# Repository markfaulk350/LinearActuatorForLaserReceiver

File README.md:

# Linear Actuator For Laser Receiver

# Todo
- See if we can use the DF Robot Voice Recognition to controll the whole thing. Look at the [pre-programmed keywords](https://wiki.dfrobot.com/SKU_SEN0539-EN_Gravity_Voice_Recognition_Module_I2C_UART#Command%20Words%2FWake-up%20Words%20%26amp%3B%20ID%20Table) to see what would work best.
- Get 4x M3 bolts for the motor. The depth is 4.5mm (0.17 in), so add the thickness of the plate. M3 x 0.5 x 8mm is best for a 0.2in plate.
- Get 3x M3 x 0.5 x 16mm bolts for the lead screw flange nut. Model the carriage so they can thread into the plastic. The flange is 0.19in thick so .6 in or 16mm is probably good. 12mm long might work but just barely, try 16mm at lowes.
- Order limit switches
- Order a linear rail. Or see if we can use the 2040 instead with a 3d printed solution.
- Order 2mm right angle pcb connector and male connector w wires
- Maybe make your own M18 adapter and put all the electronics inside it, boost converter, fuse, arduino, buck converter for arduino, etc.
- Order or make a 5mm to 3/8 coupler
- 3d print a qd mount for the laser receiver

## Custom Sensor Array vs Standard Laser Receiver on Linear Actuator
A Custom CCD or photodiode array is going to be too expensive, time consuming, and it might not work with every laser. 

On the Job, we are already moving the stick up and down, and tilting it to get the laser receiver to beep.

I propose we just hold the stick still, and have a linear actuator move the standard laser receiver until it beeps. We can tie into the laser receivers speaker wires and use that to position it perfectly. Once it's positioned, we can give the user the measurement.

### Linear Actuator
### Pros
- Cheap
- Simple to program
- Technology already exists
- Can be expanded to any length cheaply
- Can mount any laser receiver

### Cons
- Bulky
- Heavier
- Requires more power
- The physical size of the laser receiver affects the total scan area. And user needs to set the max extension so that it doesn't crash the laser receiver into the enclosure.
- Scanning is slower. 1ft per second is acceptable
  - Scanning speed largely depends on how quickly the laser receiver can detect the laser. 
- The UI is more complicated. (Calibrate, Jog, "Home", Scan)
- Different laser receivers have different speakers and signals
- If the laser receiver moves up and down, we either need to listen for the (fast, solid, slow) beeps using a microphone, or tap into the speaker wires.
- If we tap into the speaker wires, we will need to make a little radio to transmit the speaker signals to our esp32. The laser receiver will be moving up and down, we cant use a wire, it would snag or break.

# Build requirements
- Needs to scan quickly. 1ft per second is a good speed.
- Needs to move a 300g laser reeciver up and down.
- No creep. If bumped, powered off, etc. Belt drive probably wont work.
- 2 to 3 ft scan area
- Total weight under 5 pounds. Loose requirement.
- Needs to work in a dusty, hot environment.
- Encoder on stepper motor for exact position
- Maybe boost convertor for higher speeds

# Laser Receiver Dimensions
- Topcon LS-80L (NEW Model)
  - x in (Tall) | x in (Wide) | x in (Thick) | x grams (Weight)
- Topcon LS-70B (OLD Model)
  - 6.5 in (Tall) | 3 in (Wide) | 1.05 in (Thick) | 220 grams (Weight)

# Parts List
- $71 | [StepperOnline | ESS17-04](https://www.omc-stepperonline.com/ess-series-0-48nm-68oz-in-nema-17-integrated-closed-loop-stepper-servo-motor-24-36vdc-1000cpr-ess17-04)
  - [3D Model .IGS](https://www.omc-stepperonline.com/index.php?route=product/product/get_file&file=1265/ESS17-04.IGS)
  - Input Voltage: 24 - 36VDC
  - Weight: 419g
  - [SpecSheet](file:///Users/markfaulkner/Downloads/ESS17-04_07_Manual.pdf)
- $83 | [M18 HIGH OUTPUT CP3.0](https://www.milwaukeetool.com/products/48-11-1835)
  - Weight: 595g
- $8 | [M18 Adapter | Amazon](https://a.co/d/7E8KwFV)
  - Weight: 80g
- $57 | [300W Boost Converter | I7C4W008A120V-001-R | Digikey](https://www.digikey.com/en/products/detail/tdk-lambda/I7C4W008A120V-001-R/11697408)
  - Weight: 25g, 1.5 x 1.5 x 0.5 inches
  - Output Voltage: 9.6 to 48V
  - [SpecSheet](https://product.tdk.com/en/search/power/switching-power/dc-dc-converter/info?part_no=i7C4W008A120V-001-R)
- $40 | [Roton Torqspline Lead Screw, 3/8 X 1.000](https://www.roton.com/product/torqspline-steel-screw-right-60998/)
  - Weight: 368g for all 36 inches
- $20 | [Roton Torqspline Flange Nut, 3/8 X 1.000, RH, Plastic](https://www.roton.com/product/torqspline-plastic-flange-nut-right-92054/)
  - Weight: na
- $40 | [2x 2040 Aluminum V Slot 4ft | Amazon](https://a.co/d/5IGCPNE)
  - Weight: na
- $7 | [R6-2RS Bearings 3/8 ID x 7/8 OD x 9/32 | Amazon](https://a.co/d/5ckjm9j)
  - Weight: na
- $ | 
  - Weight: na
 
## Small electronics parts list
- 47k R + 10k R Voltage divider
- 1x 0.15uf [Ceramic Capacitor](https://a.co/d/4Orx2Qe)
- [MP1584EN DC-DC Buck Converter](https://a.co/d/amErUwB)

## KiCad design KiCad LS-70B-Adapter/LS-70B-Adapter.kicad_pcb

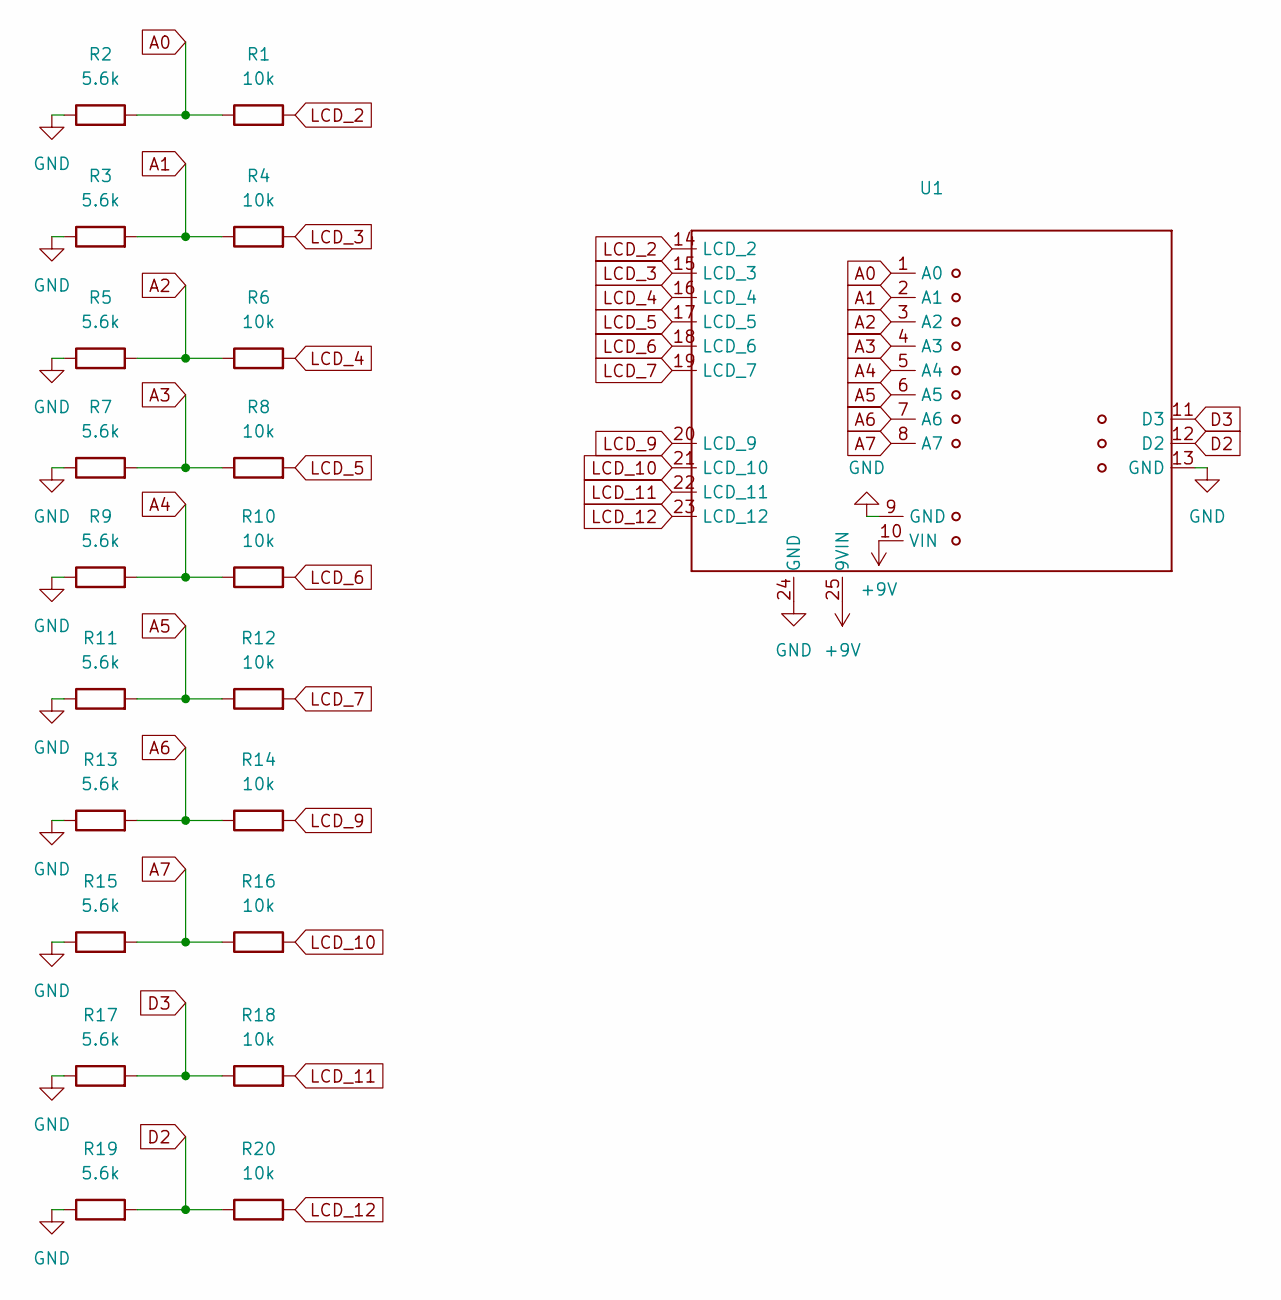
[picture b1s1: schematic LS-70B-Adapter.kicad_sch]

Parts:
R1, R4, R6, R8, R10, R12, R14, R16, R18, R20: 10k; R_0805_2012Metric_Pad1.20x1.40mm_HandSolder
R2, R3, R5, R7, R9, R11, R13, R15, R17, R19: 5.6k; R_0805_2012Metric_Pad1.20x1.40mm_HandSolder
U1: LS70B-Adapter

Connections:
+9V: U1.10 (VIN), U1.25 (9VIN)
A0: R1.1, R2.2, U1.1 (A0)
A1: R3.2, R4.1, U1.2 (A1)
A2: R5.2, R6.1, U1.3 (A2)
A3: R7.2, R8.1, U1.4 (A3)
A4: R9.2, R10.1, U1.5 (A4)
A5: R11.2, R12.1, U1.6 (A5)
A6: R13.2, R14.1, U1.7 (A6)
A7: R15.2, R16.1, U1.8 (A7)
D2: R19.2, R20.1, U1.12 (D2)
D3: R17.2, R18.1, U1.11 (D3)
GND: R2.1, R3.1, R5.1, R7.1, R9.1, R11.1, R13.1, R15.1, R17.1, R19.1, U1.9 (GND), U1.13 (GND), U1.24 (GND)
LCD_2: R1.2, U1.14 (LCD_2)
LCD_3: R4.2, U1.15 (LCD_3)
LCD_4: R6.2, U1.16 (LCD_4)
LCD_5: R8.2, U1.17 (LCD_5)
LCD_6: R10.2, U1.18 (LCD_6)
LCD_7: R12.2, U1.19 (LCD_7)
LCD_9: R14.2, U1.20 (LCD_9)
LCD_10: R16.2, U1.21 (LCD_10)
LCD_11: R18.2, U1.22 (LCD_11)
LCD_12: R20.2, U1.23 (LCD_12)

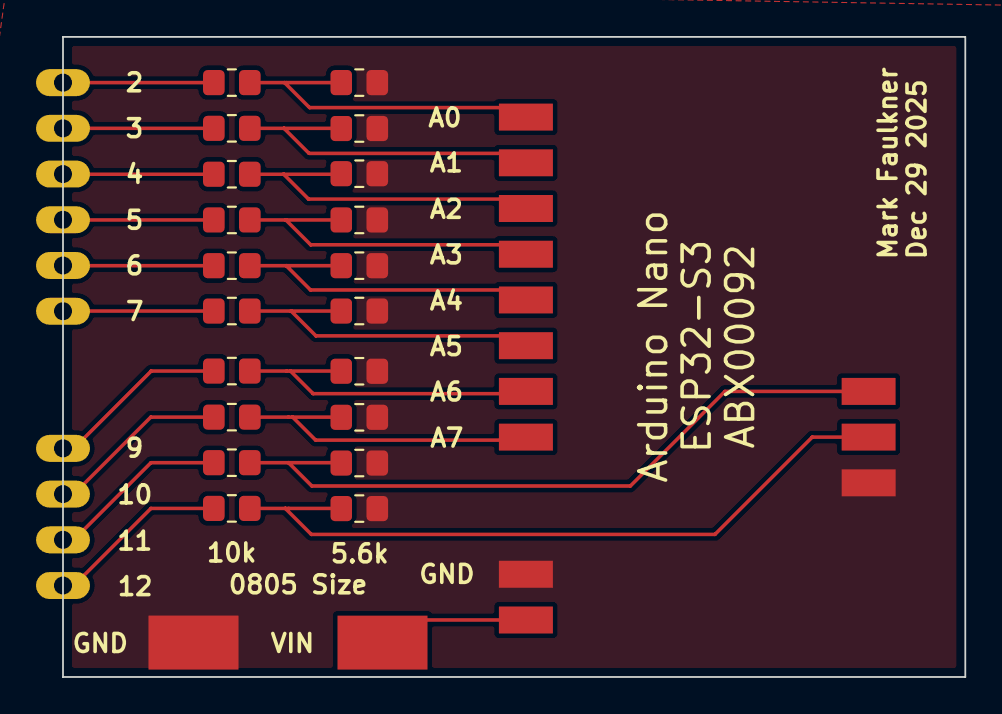
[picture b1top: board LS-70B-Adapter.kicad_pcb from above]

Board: 2 copper layers, 50.1 x 35.6 mm, 21 parts (0 on the bottom side), 22 nets.

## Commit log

2025-12-30 Added KiCad Files for PCB
